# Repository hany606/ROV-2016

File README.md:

# ROV-2016
This repo is used to archive the codes and work of Electrical team of ROV 2016 Rangers category (Hammer Heads team).

The team: https://drive.google.com/file/d/0B9RDcyLD1gKPZHUzZEJrLXlaYVE/view?usp=sharing

#### Blue.py:
It is a python library to use BlueRobotics T100 Motor with BlueESC to use with Raspberry pi or similar.

#### FinalGUI.vi:
It is the LabView Program for the GUI to control the ROV.

#### Raspberry Pi code.py:
It is the python code which is running on the Raspberry pi as the main controller.

#### PCB Folder:
It contains the PCB layouts and boards for the PCB layers we used.

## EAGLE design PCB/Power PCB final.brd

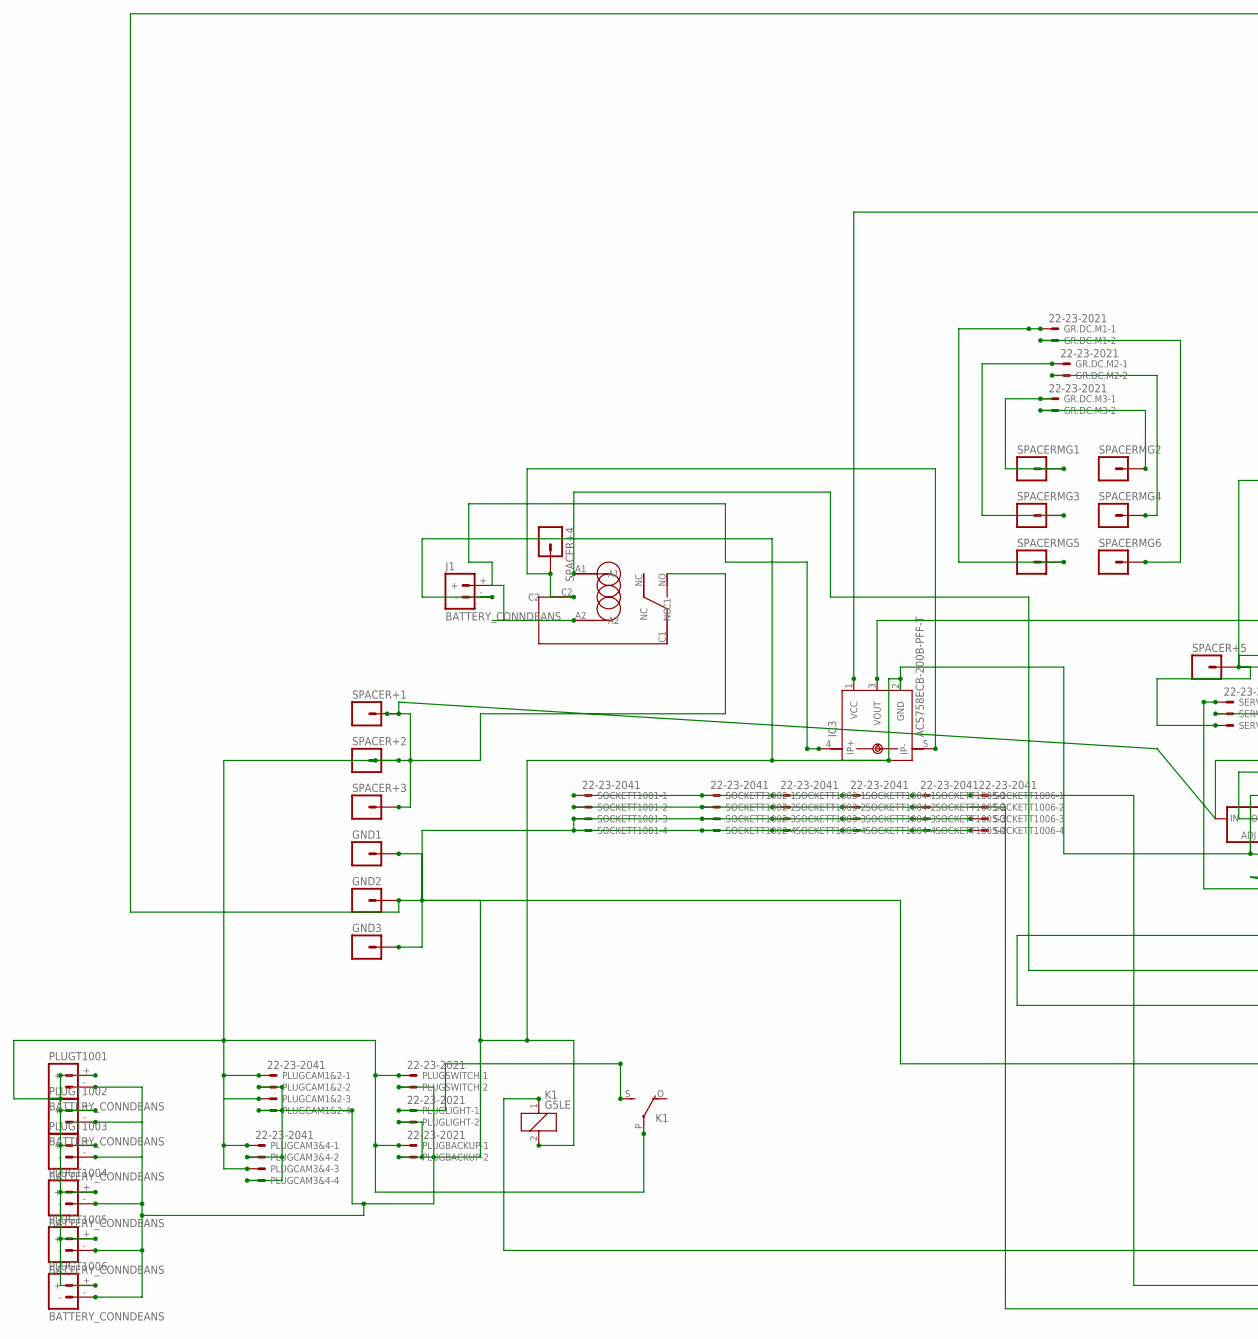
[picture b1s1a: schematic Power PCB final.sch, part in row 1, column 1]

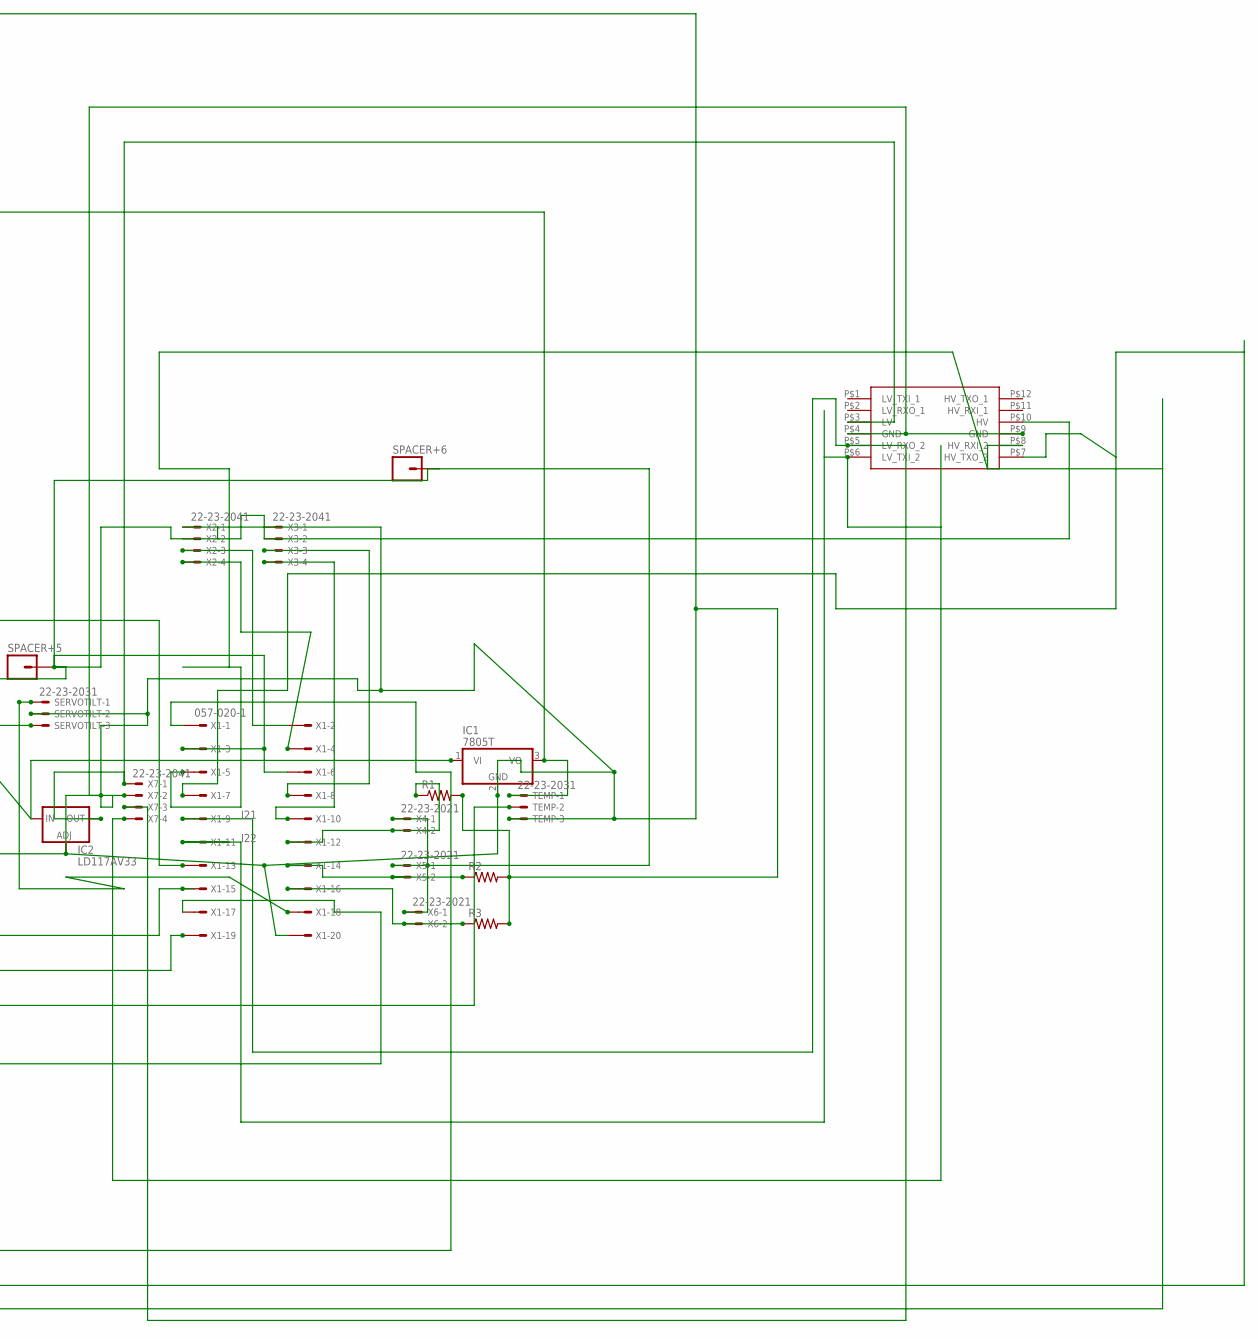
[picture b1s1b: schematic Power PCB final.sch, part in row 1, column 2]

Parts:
GND1, GND2, GND3: M01PTH_2MM; 1X01_2MM
GR.DC.M1, GR.DC.M2, GR.DC.M3: 22-23-2021
IC1: 7805T; TO220H
IC2: LD117AV33; TO220L1
IC3: ACS758ECB-200B-PFF-T; CB-PFF
J1: BATTERY_CONNDEANS; DEANS
K1: G5LE
PLUGBACKUP: 22-23-2021
PLUGCAM1&2, PLUGCAM3&4: 22-23-2041
PLUGLIGHT: 22-23-2021
PLUGSWITCH: 22-23-2021
PLUGT1001, PLUGT1002, PLUGT1003, PLUGT1004, PLUGT1005, PLUGT1006: BATTERY_CONNDEANS; DEANS
R1, R2, R3: R-US_0207/10; 0207/10
SERVOTILT: 22-23-2031
SOCKETT1001, SOCKETT1002, SOCKETT1003, SOCKETT1004, SOCKETT1005, SOCKETT1006: 22-23-2041
SPACER+1, SPACER+2, SPACER+3, SPACER+4, SPACER+5, SPACER+6: M01PTH_2MM; 1X01_2MM
SPACERMG1, SPACERMG2, SPACERMG3, SPACERMG4, SPACERMG5, SPACERMG6: M01PTH_2MM; 1X01_2MM
TEMP: 22-23-2031
U$1: 30A_RELAY
U$2: LOGIC_LEVEL_CONVERTER
X1: 057-020-1
X2, X3, X7: 22-23-2041
X4, X5, X6: 22-23-2021

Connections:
I21: U$2.P$5 (LV_RXO_2), X1.9, X7.3
I22: U$2.P$6 (LV_TXI_2), X1.11, X7.4
unnamed: SOCKETT1001.1, SOCKETT1002.1, SOCKETT1003.1, SOCKETT1004.1, SOCKETT1005.1, SOCKETT1006.1, U$2.P$7 (HV_TXO_2), X1.7
unnamed: X1.4, X2.4
unnamed: IC3.3 (VOUT), X1.13
unnamed: SOCKETT1001.2, SOCKETT1002.2, SOCKETT1003.2, SOCKETT1004.2, SOCKETT1005.2, SOCKETT1006.2, U$2.P$8 (HV_RXI_2), X1.5
unnamed: GR.DC.M3.1, SPACERMG1.1
unnamed: K1.1, X1.1
unnamed: TEMP.2, X1.15
unnamed: K1.S, PLUGLIGHT.1
unnamed: GR.DC.M3.2, SPACERMG2.1
unnamed: GR.DC.M2.2, SPACERMG4.1
unnamed: GR.DC.M2.1, SPACERMG3.1
unnamed: GR.DC.M1.2, SPACERMG6.1
unnamed: GR.DC.M1.1, SPACERMG5.1
unnamed: GND1.1, GND2.1, GND3.1, IC1.2 (GND), IC2.1 (ADJ), IC3.2 (GND), J1.-, K1.2, PLUGBACKUP.2, PLUGCAM1&2.2, PLUGCAM1&2.4, PLUGCAM3&4.2, PLUGCAM3&4.4, PLUGLIGHT.2, PLUGSWITCH.2, PLUGT1001.-, PLUGT1002.-, PLUGT1003.-, PLUGT1004.-, PLUGT1005.-, PLUGT1006.-, R1.2, R2.2, R3.2, SERVOTILT.2, SOCKETT1001.3, SOCKETT1001.4, SOCKETT1002.3, SOCKETT1002.4, SOCKETT1003.3, SOCKETT1003.4, SOCKETT1004.3, SOCKETT1004.4, SOCKETT1005.3, SOCKETT1005.4, SOCKETT1006.3, SOCKETT1006.4, TEMP.3, U$2.P$4 (GND), U$2.P$9 (GND), X1.17, X1.20, X2.1, X3.1, X7.2
unnamed: IC3.5 (IP-), SPACER+4.1, U$1.C2
unnamed: X1.10, X3.4
unnamed: X1.8, X3.3
unnamed: X1.2, X2.3
unnamed: SERVOTILT.1, X1.18
unnamed: IC2.2 (OUT), U$2.P$3 (LV), X7.1
unnamed: U$1.A1, X1.19
unnamed: IC1.3 (VO), IC3.1 (VCC), TEMP.1
unnamed: IC3.4 (IP+), J1.+, U$1.A2
unnamed: IC1.1 (VI), IC2.3 (IN), K1.P, PLUGBACKUP.1, PLUGCAM1&2.1, PLUGCAM1&2.3, PLUGCAM3&4.1, PLUGCAM3&4.3, PLUGSWITCH.1, PLUGT1001.+, PLUGT1002.+, PLUGT1003.+, PLUGT1004.+, PLUGT1005.+, PLUGT1006.+, SPACER+1.1, SPACER+2.1, SPACER+3.1, U$1.NO
unnamed: R1.1, X1.12, X4.2
unnamed: R2.1, X1.14, X5.2
unnamed: R3.1, X1.16, X6.2
unnamed: SERVOTILT.3, SPACER+5.1, SPACER+6.1, U$2.P$10 (HV), X1.3, X1.6, X2.2, X3.2, X4.1, X5.1, X6.1

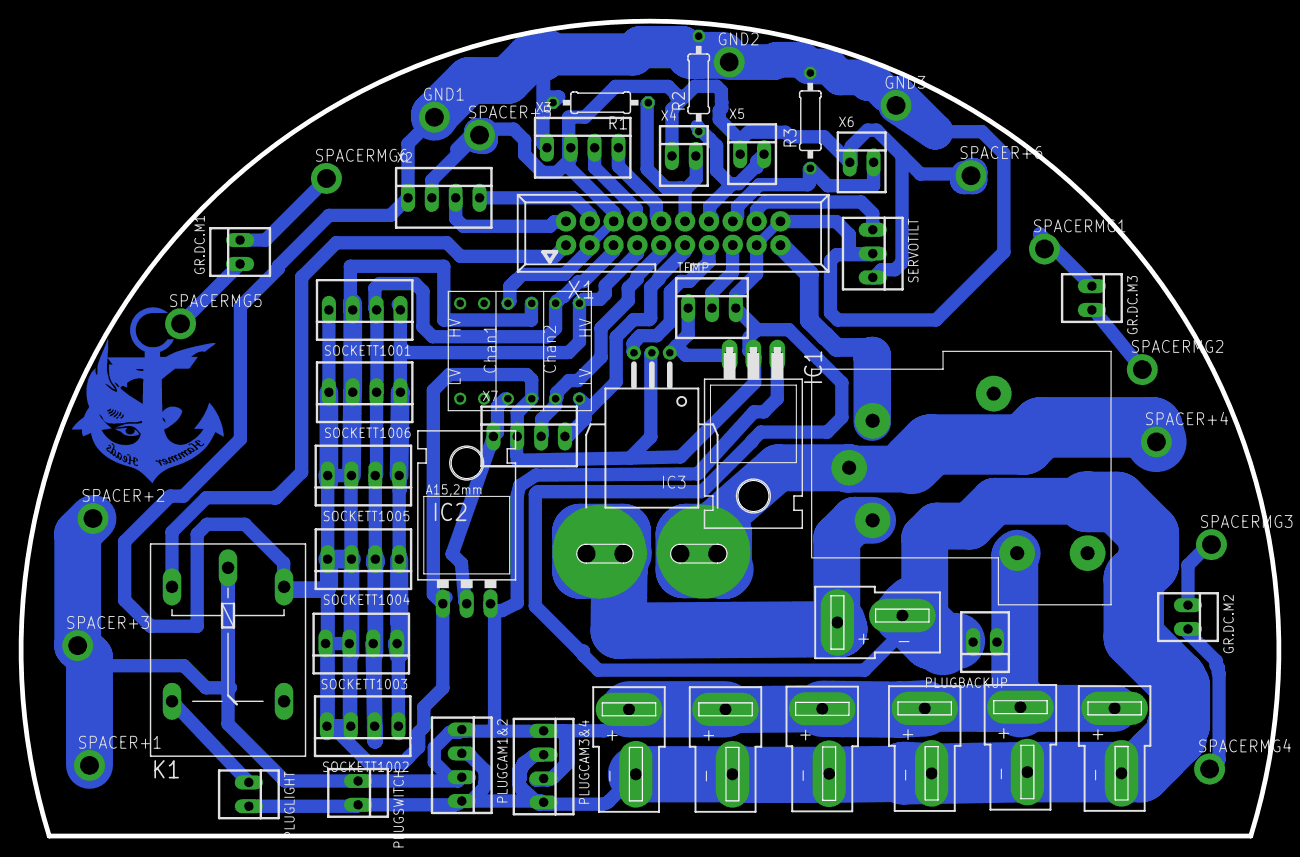
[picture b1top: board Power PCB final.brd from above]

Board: 2 copper layers, 134.0 x 86.8 mm, 54 parts (0 on the bottom side), 30 nets.

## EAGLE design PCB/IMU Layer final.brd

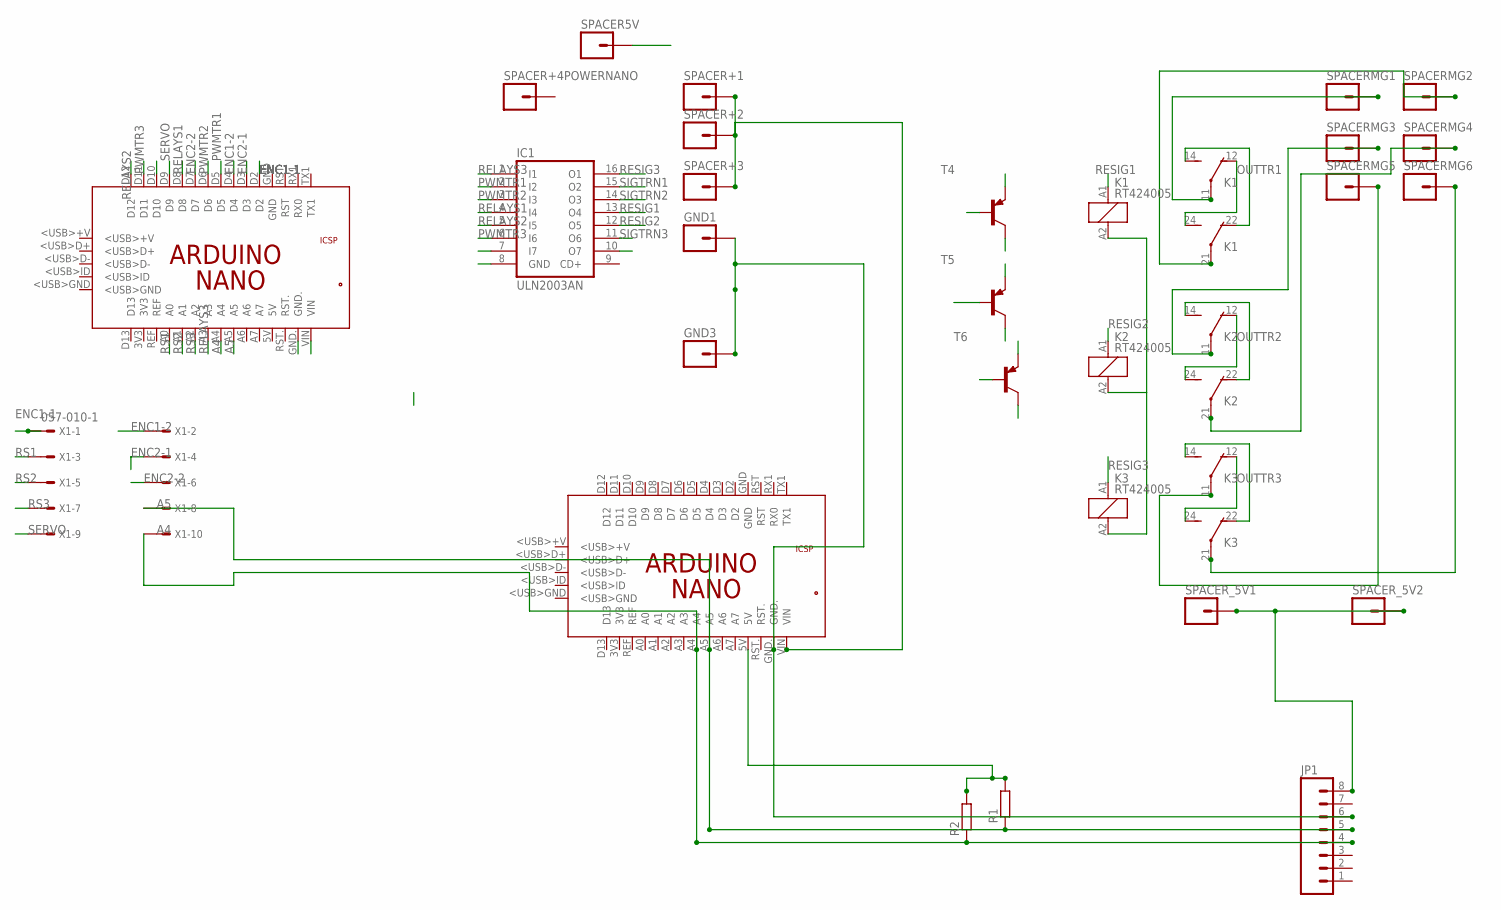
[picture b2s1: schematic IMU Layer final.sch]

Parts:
GND1, GND3: M01PTH_2MM; 1X01_2MM
IC1: ULN2003AN; DIL16
JP1: M08LONGPADS; 1X08_LONGPADS
K1, K2, K3: RT424005; RT2C/O
PCB1, PCB3: ARDUINO_NANO
R1, R2: R-EU_0207/12; 0207/12
SPACER5V: M01PTH_2MM; 1X01_2MM
SPACER+1, SPACER+2, SPACER+3, SPACER+4POWERNANO: M01PTH_2MM; 1X01_2MM
SPACERMG1, SPACERMG2, SPACERMG3, SPACERMG4, SPACERMG5, SPACERMG6: M01PTH_2MM; 1X01_2MM
SPACER_5V1, SPACER_5V2: M01PTH_2MM; 1X01_2MM
T4, T5, T6: -PNP-TO218; TO218
X1: 057-010-1

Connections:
5V: JP1.8, SPACER5V.1, SPACER_5V1.1, SPACER_5V2.1
A4: JP1.4, PCB1.A4, PCB3.A4, R2.1, X1.10
A5: JP1.5, PCB1.A5, PCB3.A5, R1.1, X1.8
ENC1-1: PCB1.D2, X1.1
ENC1-2: PCB1.D4, X1.2
ENC2-1: PCB1.D3, X1.4
ENC2-2: PCB1.D7, X1.6
GND: GND1.1, GND3.1, IC1.8 (GND), JP1.6, PCB1.GND., PCB3.GND., T4.3 (E), T5.3 (E), T6.3 (E)
unnamed: K1.11, SPACERMG1.1
unnamed: K1.21, SPACERMG2.1
unnamed: PCB3.5V, R1.2, R2.2
unnamed: K2.11, SPACERMG3.1
unnamed: K2.21, SPACERMG4.1
unnamed: K3.11, SPACERMG5.1
unnamed: K3.21, SPACERMG6.1
OUTTR1: K1.12 (O), K1.24 (S), T4.2 (C)
OUTTR2: K2.12 (O), K2.24 (S), T5.2 (C)
OUTTR3: K3.12 (O), K3.24 (S), T6.2 (C)
POWER: K1.14 (S), K1.22 (O), K1.A2 (2), K2.14 (S), K2.22 (O), K2.A2 (2), K3.14 (S), K3.22 (O), K3.A2 (2), PCB1.VIN, PCB3.VIN, SPACER+1.1, SPACER+2.1, SPACER+3.1
PWMTR1: IC1.2 (I2), PCB1.D5
PWMTR2: IC1.3 (I3), PCB1.D6
PWMTR3: IC1.6 (I6), PCB1.D11
RELAYS1: IC1.4 (I4), PCB1.D8
RELAYS2: IC1.5 (I5), PCB1.D12
RELAYS3: IC1.1 (I1), PCB1.A3
RESIG1: IC1.13 (O4), K1.A1 (1)
RESIG2: IC1.12 (O5), K2.A1 (1)
RESIG3: IC1.16 (O1), K3.A1 (1)
RS1: PCB1.A0, X1.3
RS2: PCB1.A1, X1.5
RS3: PCB1.A2, X1.7
SERVO: PCB1.D9, X1.9
SIGTRN1: IC1.15 (O2), T4.1 (B)
SIGTRN2: IC1.14 (O3), T5.1 (B)
SIGTRN3: IC1.11 (O6), T6.1 (B)

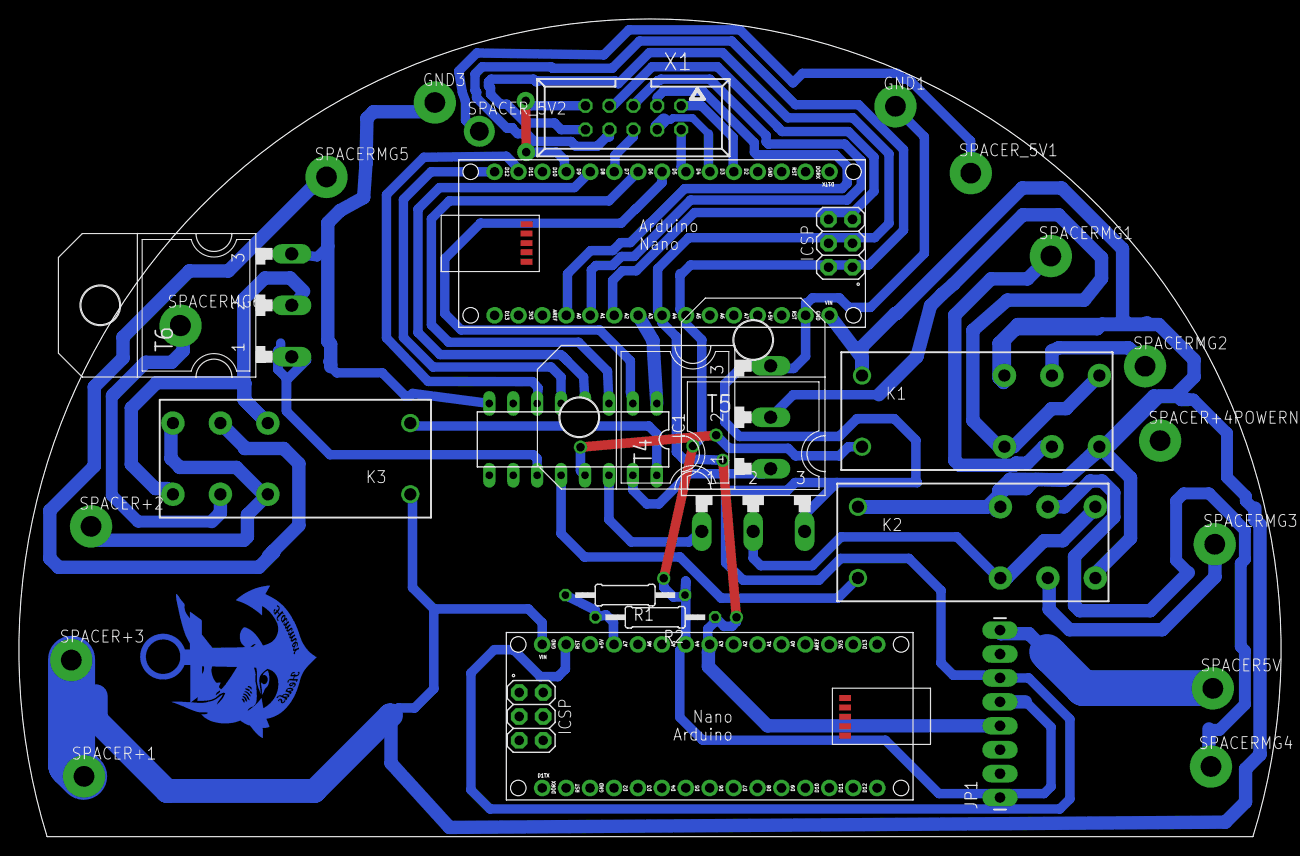
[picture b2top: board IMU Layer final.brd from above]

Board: 2 copper layers, 133.9 x 86.7 mm, 28 parts (0 on the bottom side), 35 nets.

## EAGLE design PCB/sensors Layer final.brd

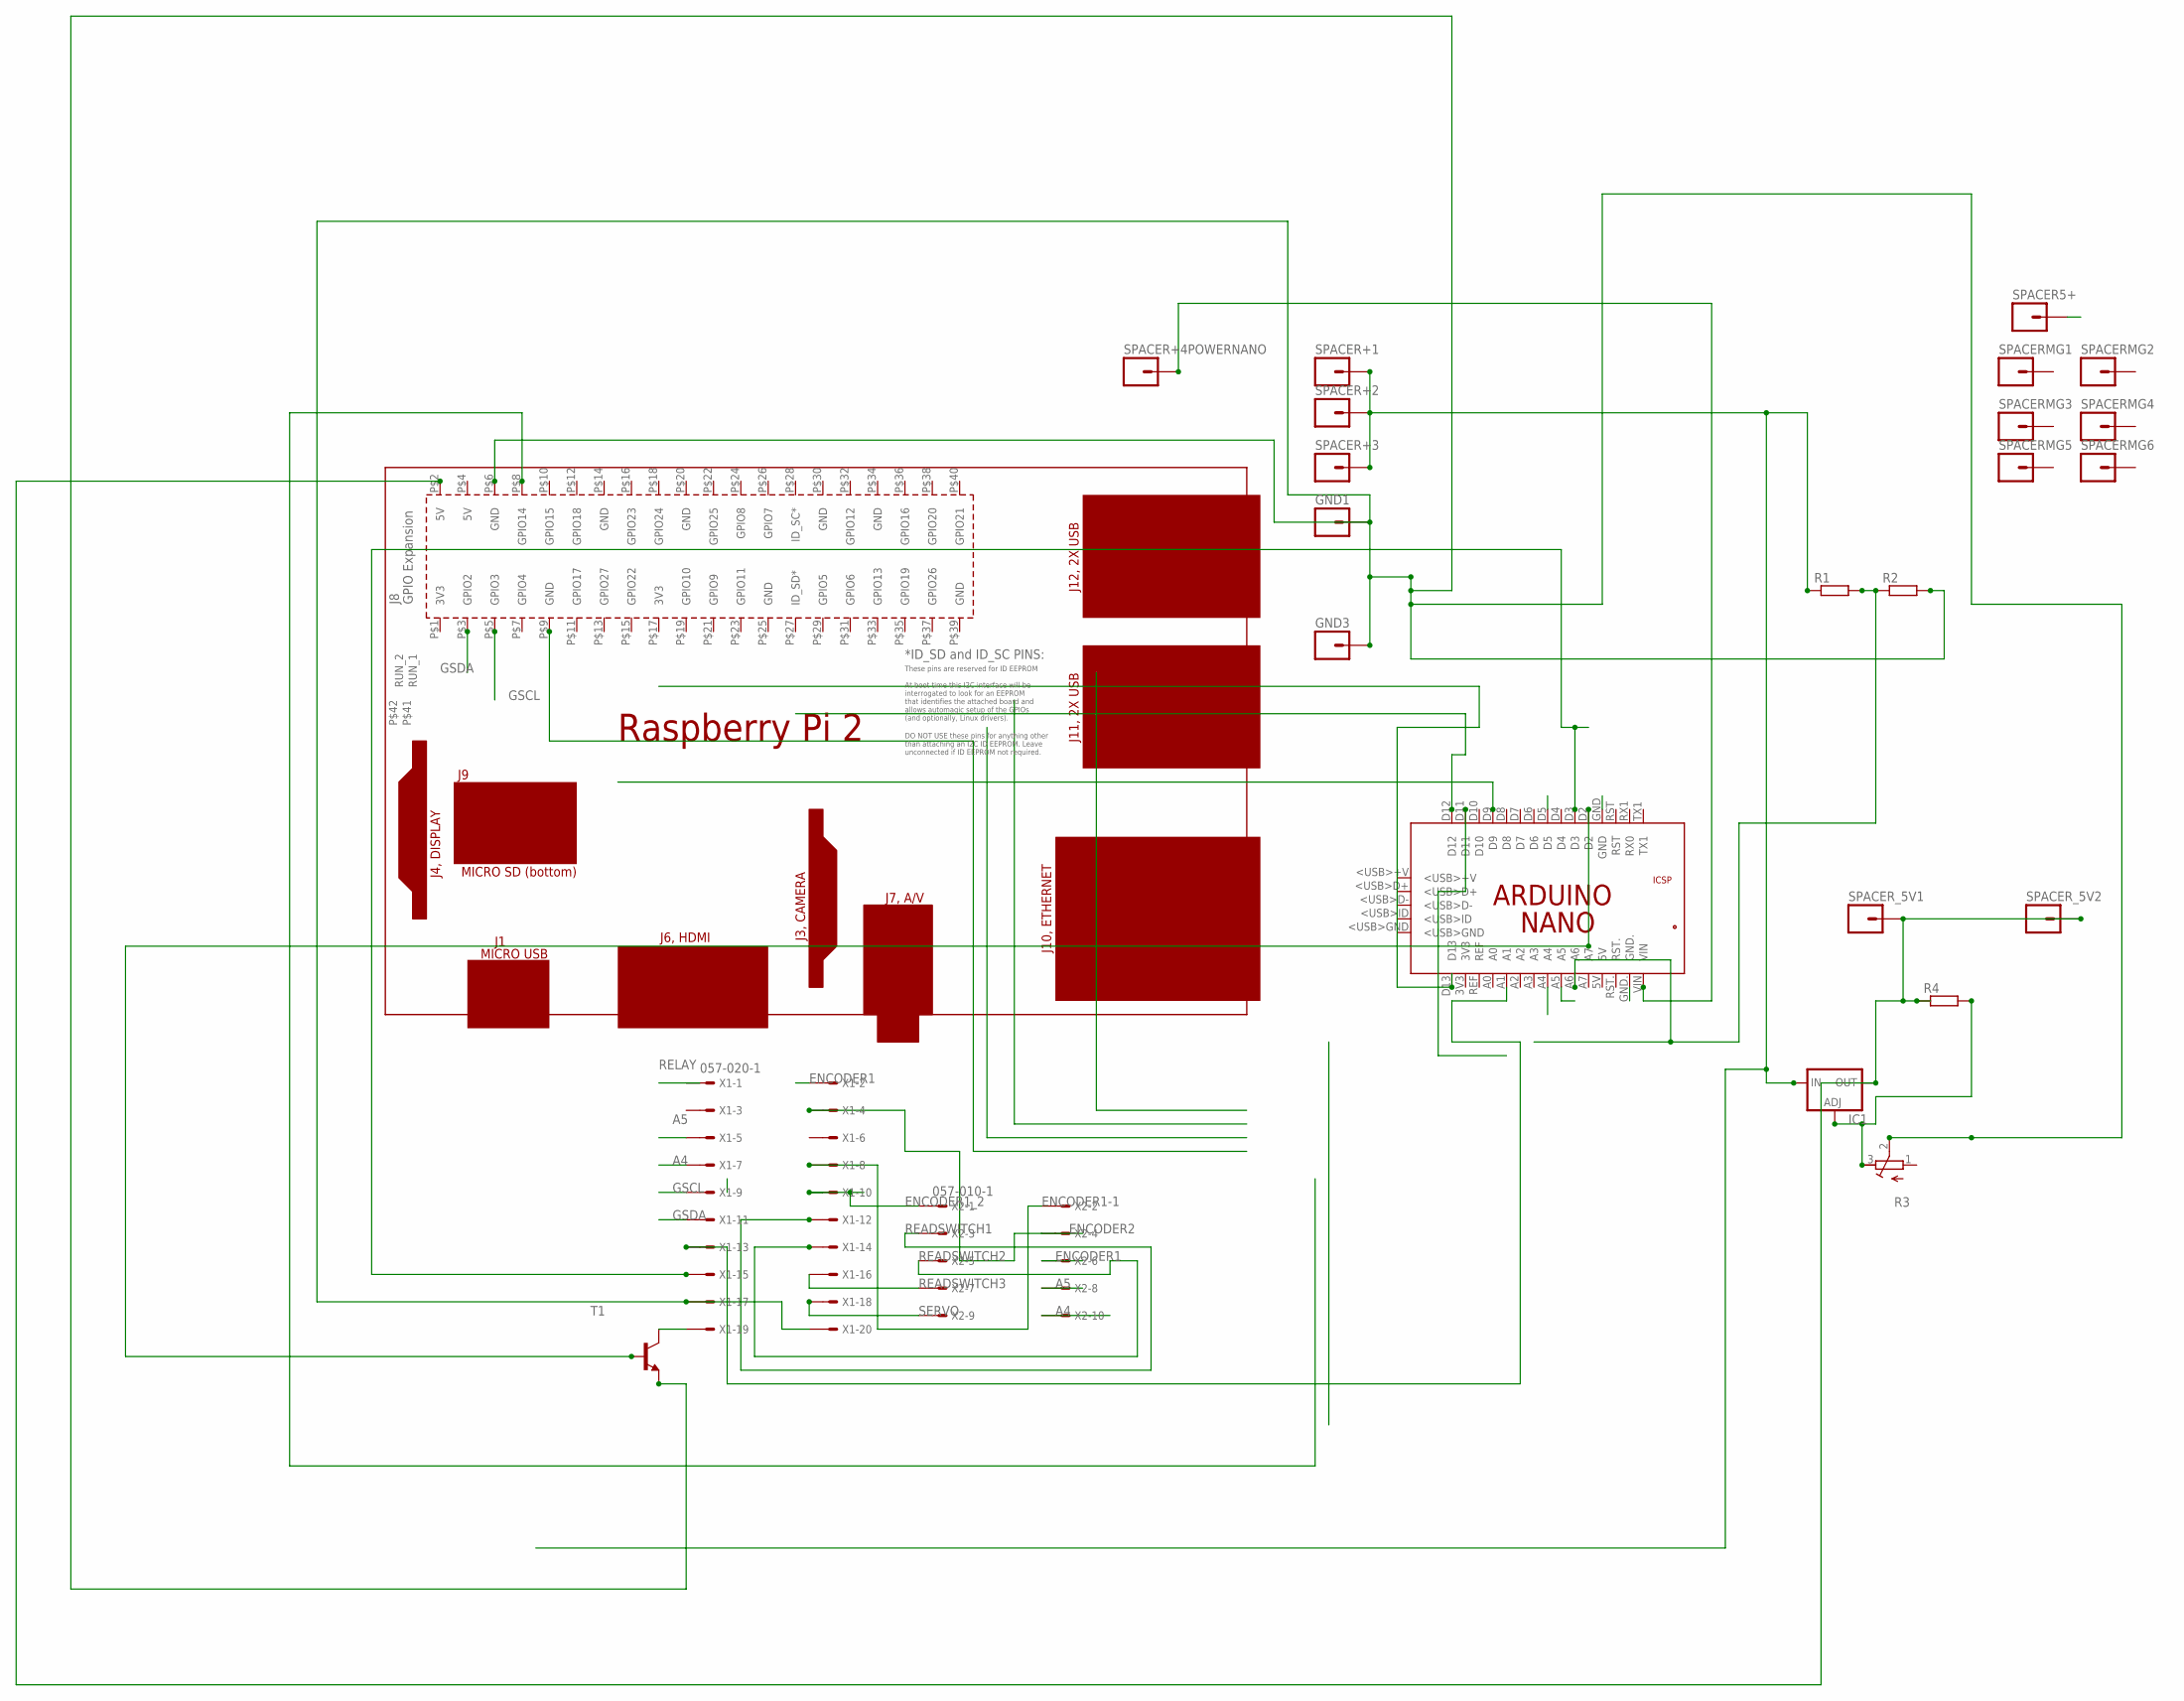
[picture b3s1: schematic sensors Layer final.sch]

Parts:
GND1, GND3: M01PTH_2MM; 1X01_2MM
IC1: LM138-TO3; TO3-K02
PCB1: RPI2
PCB2: ARDUINO_NANO
R1, R2, R4: R-EU_0207/10; 0207/10
R3: R-TRIMM64W; RTRIM64W
SPACER5+: M01PTH_2MM; 1X01_2MM
SPACER+1, SPACER+2, SPACER+3, SPACER+4POWERNANO: M01PTH_2MM; 1X01_2MM
SPACERMG1, SPACERMG2, SPACERMG3, SPACERMG4, SPACERMG5, SPACERMG6: M01PTH_2MM; 1X01_2MM
SPACER_5V1, SPACER_5V2: M01PTH_2MM; 1X01_2MM
T1: BC547-NPN-TO92-CBE; TO92-CBE
X1: 057-020-1
X2: 057-010-1

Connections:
5V: IC1.3 (OUT), PCB1.P$2 (5V), R4.1, SPACER5+.1, SPACER_5V1.1, SPACER_5V2.1
A4: PCB2.A4, X1.7, X2.10
A5: PCB2.A5, X1.5, X2.8
ENCODER1: X1.2, X2.6
ENCODER1-1: X1.8, X2.2
ENCODER1_2: X1.10, X2.1
ENCODER2: X1.4, X2.4
GND: GND1.1, GND3.1, PCB1.P$6 (GND), PCB2.GND, PCB2.GND., R2.2, R3.2 (S), T1.E, X1.17, X1.20
GSCL: PCB1.P$5 (GPIO3), X1.9
GSDA: PCB1.P$3 (GPIO2), X1.11
unnamed: PCB2.D2, T1.B
unnamed: PCB2.A1, X1.13
unnamed: T1.C, X1.19
unnamed: IC1.1 (IN), R1.1, SPACER+1.1, SPACER+2.1, SPACER+3.1
unnamed: PCB2.VIN, SPACER+4POWERNANO.1
unnamed: PCB2.A6, R1.2, R2.1
unnamed: PCB2.D3, X1.15
unnamed: IC1.2 (ADJ), R3.3 (A), R4.2
READSWITCH1: X1.12, X2.3
READSWITCH2: X1.14, X2.5
READSWITCH3: X1.16, X2.7
RELAY: PCB2.D5, X1.1
SERVO: X1.18, X2.9

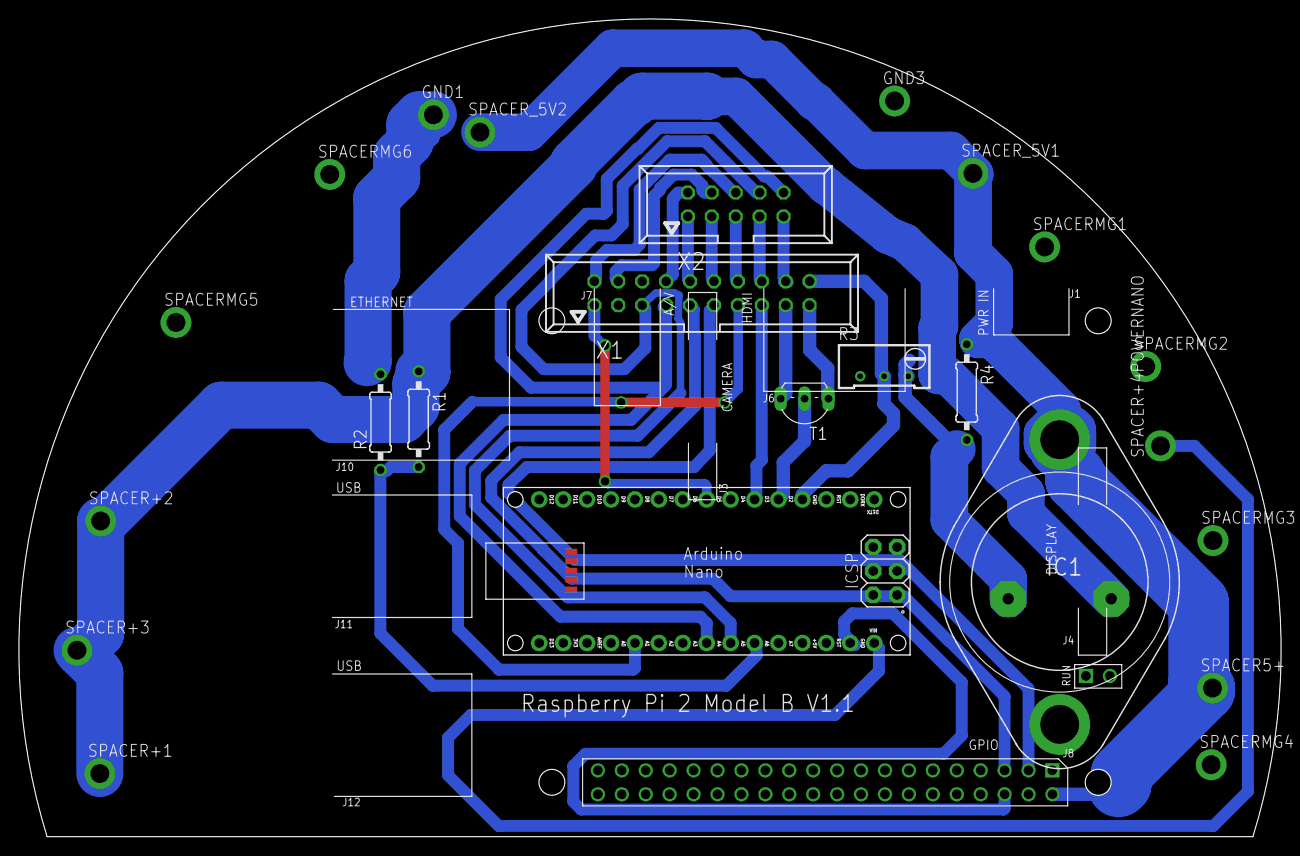
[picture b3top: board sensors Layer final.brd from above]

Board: 2 copper layers, 133.9 x 86.7 mm, 25 parts (0 on the bottom side), 23 nets.

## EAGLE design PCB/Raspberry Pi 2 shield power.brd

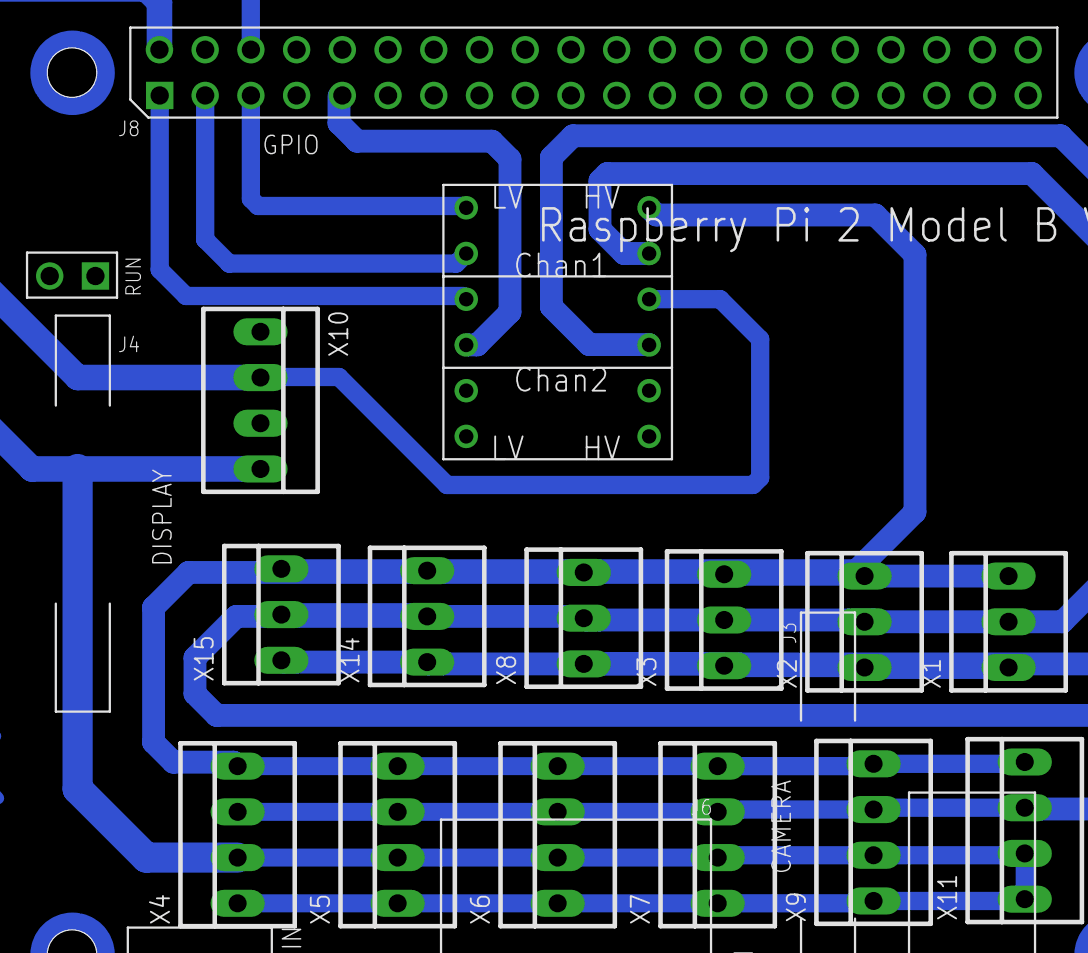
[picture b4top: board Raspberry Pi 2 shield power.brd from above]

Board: 2 copper layers, 15 parts (0 on the bottom side), 9 nets.

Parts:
PCB1: RPI2
U$2: LOGIC_LEVEL_CONVERTER
X1, X2, X3, X8, X14, X15: 22-23-2031
X4, X5, X6, X7, X9, X10, X11: 22-23-2041

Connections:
unnamed: PCB1.P$5, U$2.P$1
unnamed: U$2.P$9, X1.1, X2.1, X3.1, X8.1, X14.1, X15.1
unnamed: PCB1.P$3, U$2.P$2
unnamed: PCB1.P$1, U$2.P$3
unnamed: PCB1.P$2, U$2.P$10, X10.2
unnamed: U$2.P$12, X1.3, X2.3, X3.3, X4.4, X5.4, X6.4, X7.4, X8.3, X9.4, X11.4, X14.3, X15.3
unnamed: U$2.P$11, X1.2, X2.2, X3.2, X4.3, X5.3, X6.3, X7.3, X8.2, X9.3, X11.3, X14.2, X15.2
unnamed: PCB1.P$6, X4.1, X4.2, X5.1, X5.2, X6.1, X6.2, X7.1, X7.2, X9.1, X9.2, X10.4, X11.1, X11.2
unnamed: PCB1.P$9, U$2.P$4

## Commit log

2019-01-04 Upload codes
2019-01-04 add PCB files
2019-01-19 Add technical Report

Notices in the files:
parts and their libraries:
SparkFun-Connectors: Licensing: Creative Commons ShareAlike 4.0 International - https://creativecommons.org/licenses/by-sa/4.0
